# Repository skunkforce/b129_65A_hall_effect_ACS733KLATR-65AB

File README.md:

# edgy_board number b129
This design is part of the [edgy board project](https://github.com/skunkforce/edgy_boards).

# getting started
This repository uses submodules. After cloning use the command 

```$ git submodule update --init --recursive```

to pull the submodules before opening the project with kicad. 

# Tests
Tests can be found in [TESTS.md](TESTS.md)

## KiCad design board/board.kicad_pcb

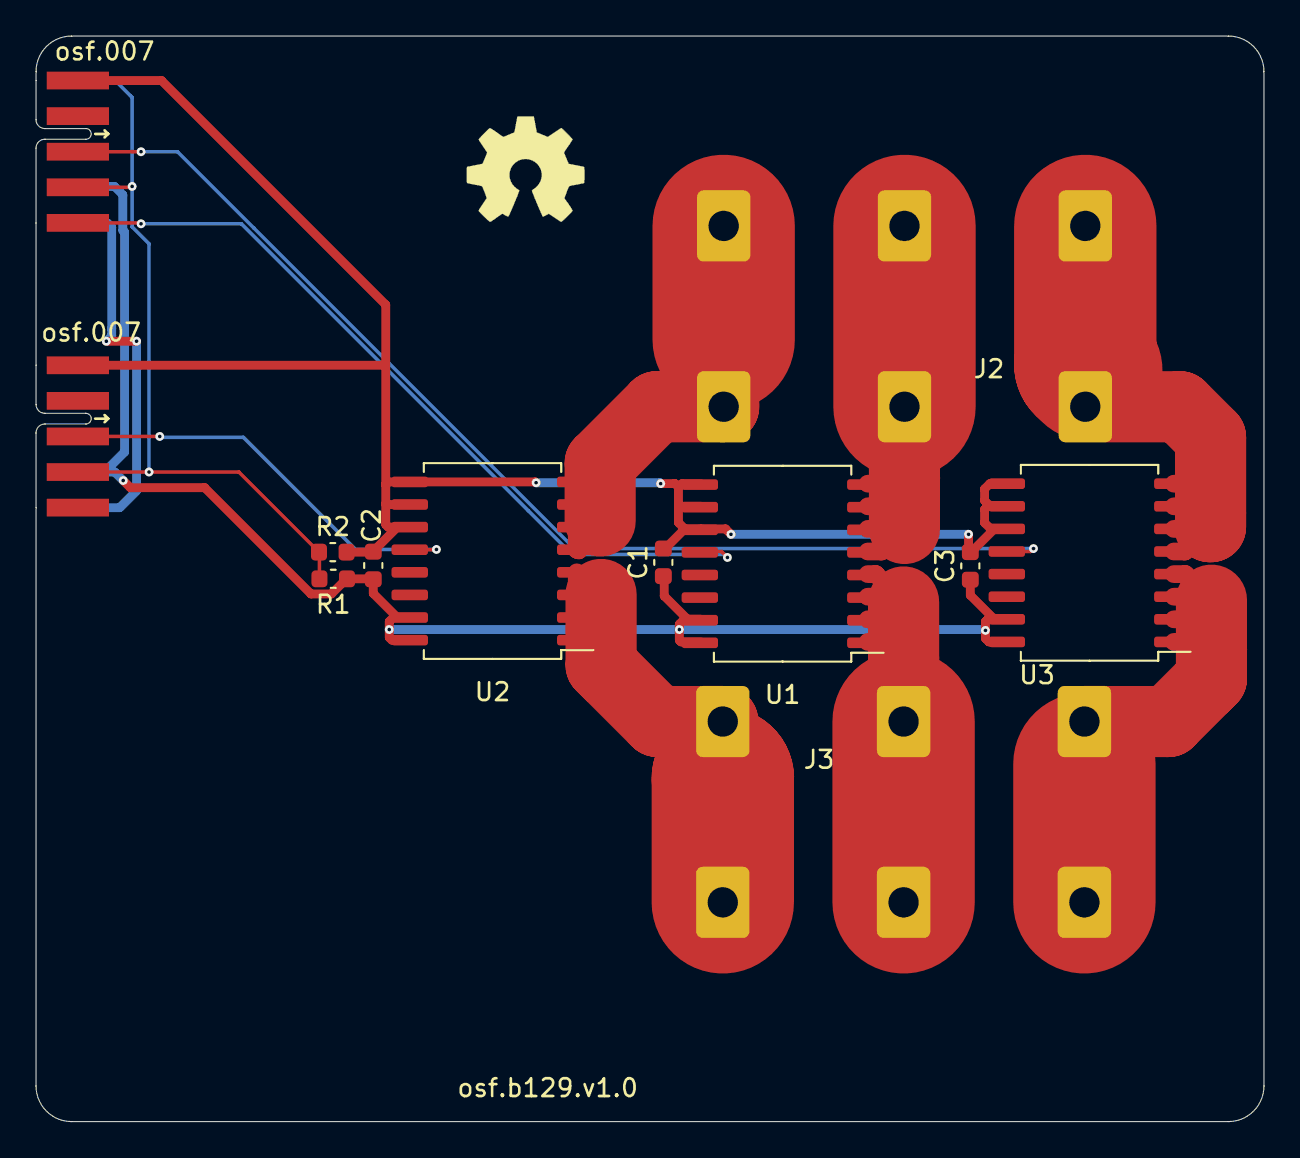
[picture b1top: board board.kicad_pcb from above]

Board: 2 copper layers, 69.0 x 61.0 mm, 13 parts (0 on the bottom side), 13 nets.

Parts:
C1, C2, C3: 100nF; C_0603_1608Metric
J1, J4: 007_ADC; on_edge_2x05_device
J2, J3: VP0365540000G
LOGO1: Logo_Open_Hardware_Small; OSHW-Symbol_6.7x6mm_SilkScreen
R1, R2: 10k; C_0603_1608Metric
U1, U2, U3: ACS733KLATR-65AB-T; SOIC-16W_6.5x12.8mm_P1.27mm

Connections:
/hall1/I+: J3.1, U2.1 (IP+), U2.2 (IP+), U2.3 (IP+), U2.4 (IP+)
/hall1/I-: J2.3, U2.5 (IP-), U2.6 (IP-), U2.7 (IP-), U2.8 (IP-)
/hall1/VIOUT: J4.3 (ADC0), U2.12 (VIOUT)
/hall2/I+: J3.3, U3.1 (IP+), U3.2 (IP+), U3.3 (IP+), U3.4 (IP+)
/hall2/I-: J2.1, U3.5 (IP-), U3.6 (IP-), U3.7 (IP-), U3.8 (IP-)
/hall2/VIOUT: J1.3 (ADC0), U3.12 (VIOUT)
/hall/I+: J3.2, U1.1 (IP+), U1.2 (IP+), U1.3 (IP+), U1.4 (IP+)
/hall/I-: J2.2, U1.5 (IP-), U1.6 (IP-), U1.7 (IP-), U1.8 (IP-)
/hall/VCC: C1.1, C2.1, C3.1, J1.9 (3.3V), J4.9 (3.3V), R1.1, U1.15 (VCC), U1.16 (VCC), U2.15 (VCC), U2.16 (VCC), U3.15 (VCC), U3.16 (VCC)
/hall/VIOUT: J1.5 (ADC2), U1.12 (VIOUT)
GND: C1.2, C2.2, C3.2, J1.1 (GND), J4.1 (GND), R2.2, U1.9 (GND), U1.10 (GND), U1.11 (PROGRAM), U2.9 (GND), U2.10 (GND), U2.11 (PROGRAM), U3.9 (GND), U3.10 (GND), U3.11 (PROGRAM)
unnamed: J1.4 (ADC1), J1.6 (ADC3), J4.4 (ADC1), R1.2, R2.1
unnamed: J1.10 (5V), J4.10 (5V)

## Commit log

2023-05-07 initial
